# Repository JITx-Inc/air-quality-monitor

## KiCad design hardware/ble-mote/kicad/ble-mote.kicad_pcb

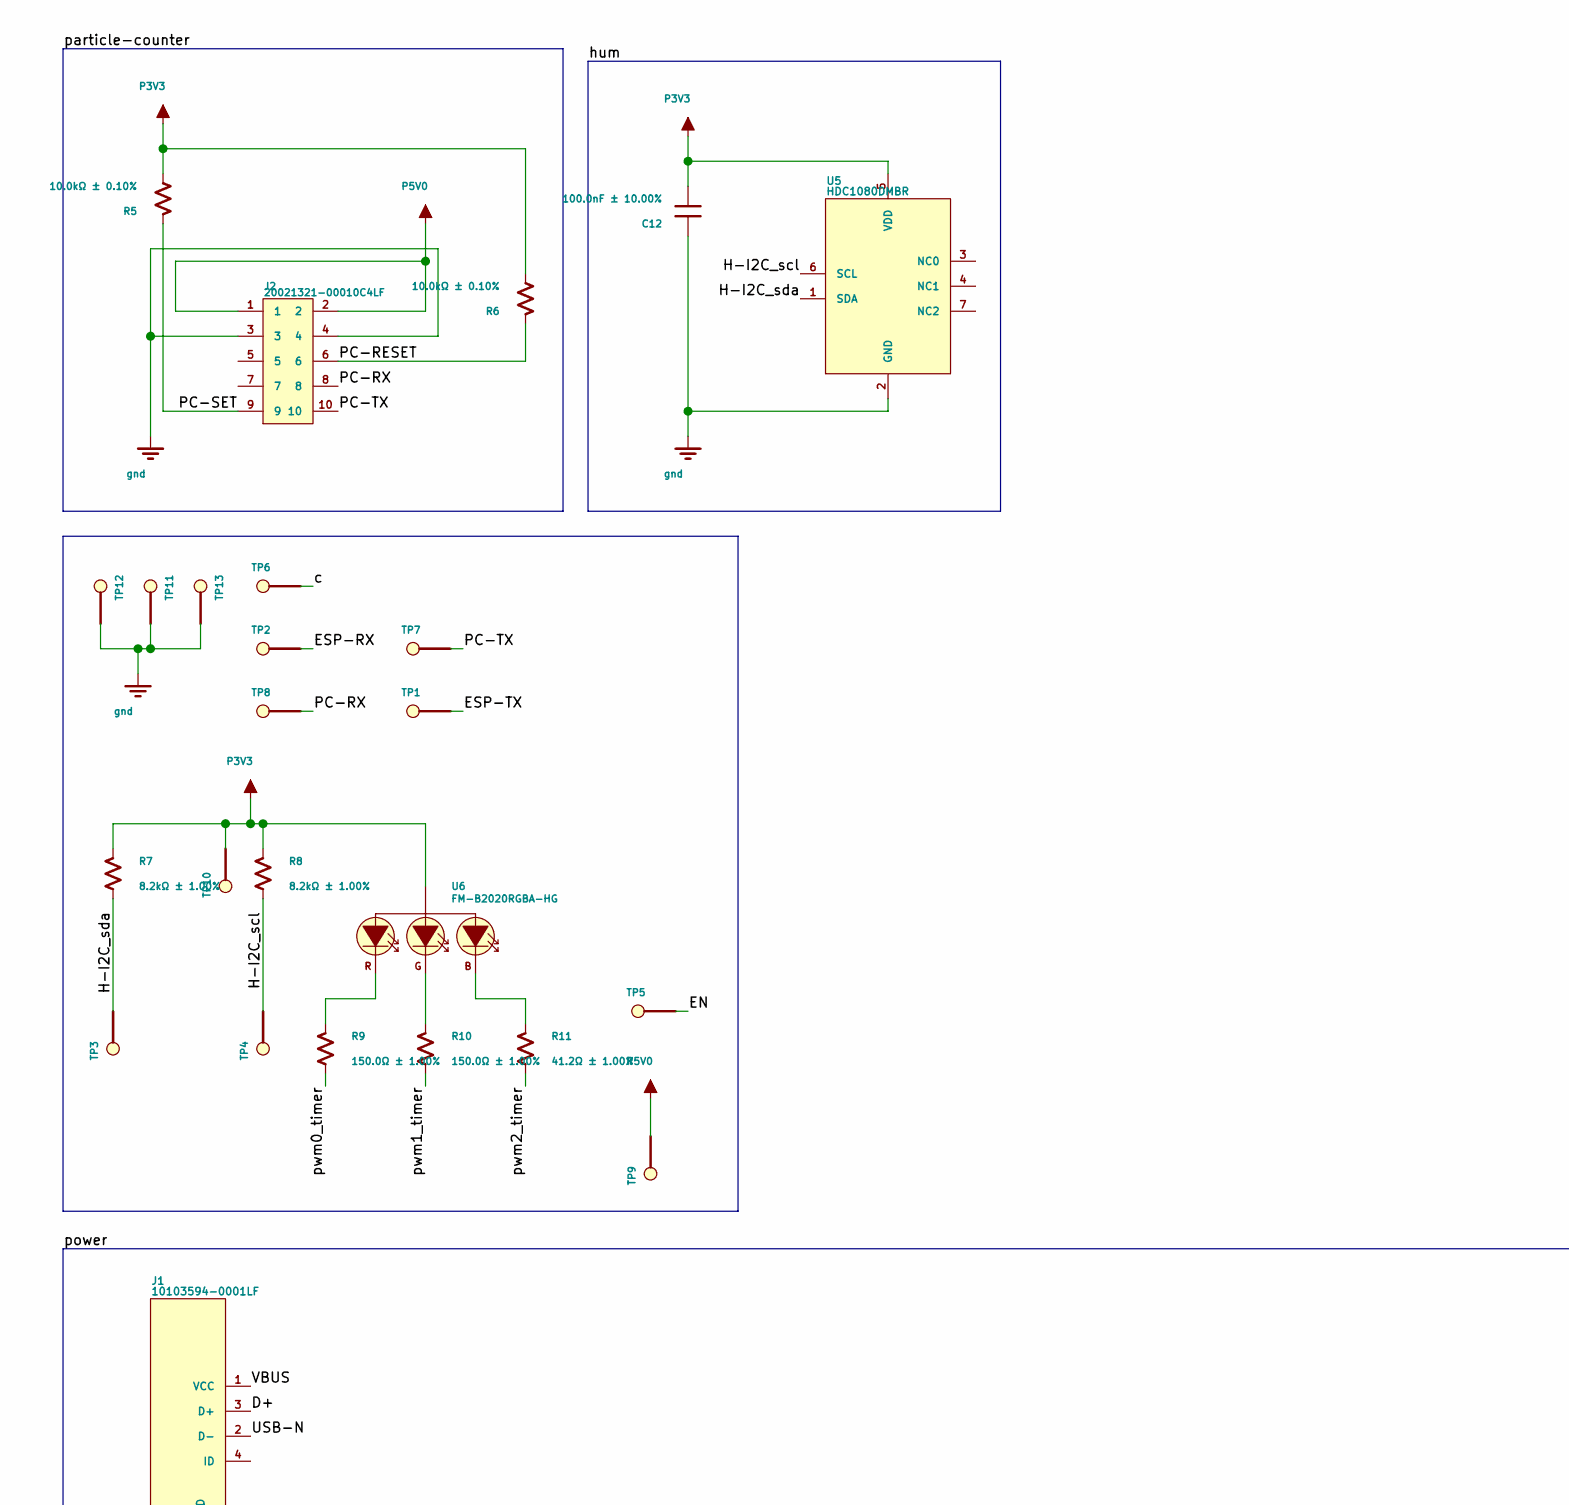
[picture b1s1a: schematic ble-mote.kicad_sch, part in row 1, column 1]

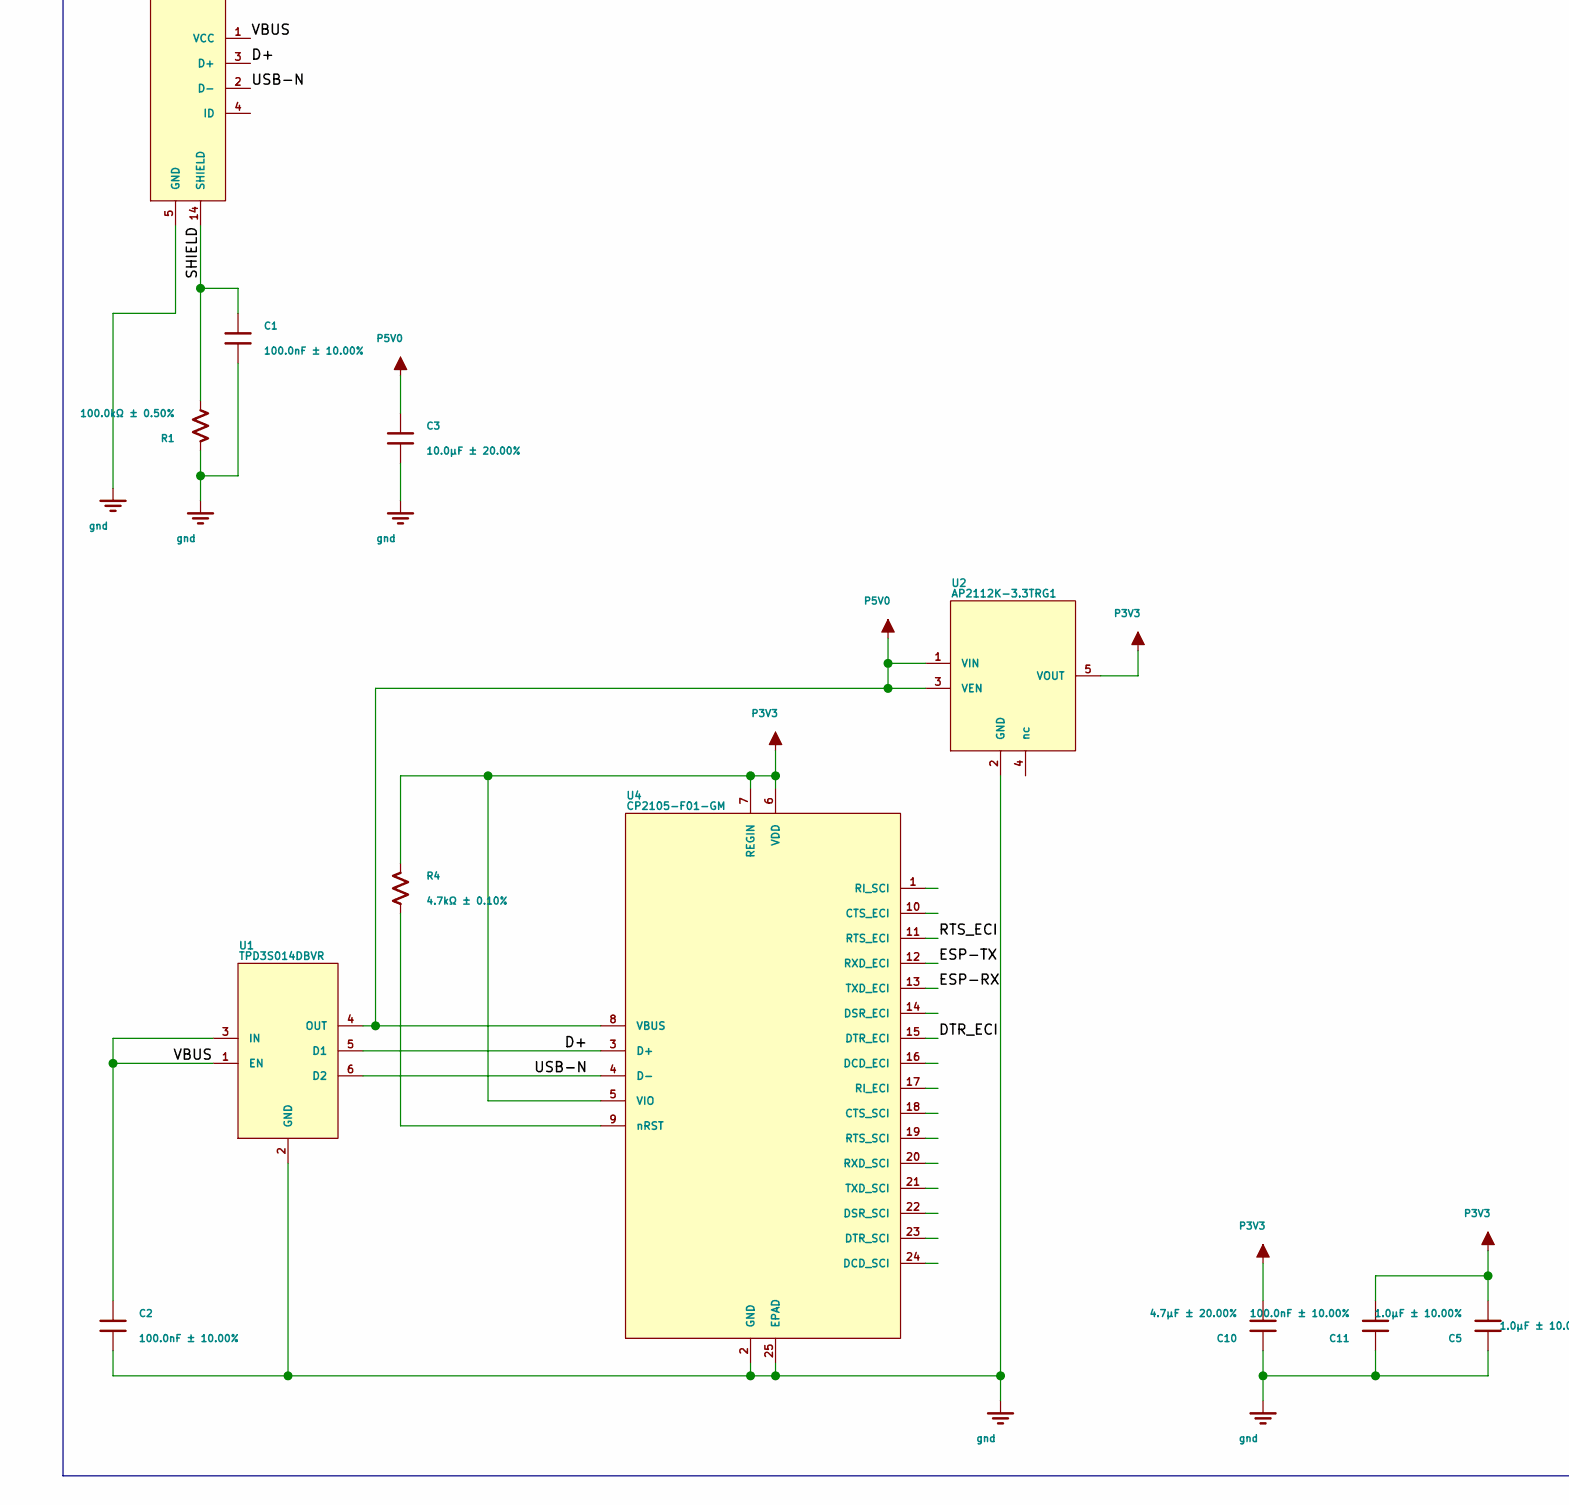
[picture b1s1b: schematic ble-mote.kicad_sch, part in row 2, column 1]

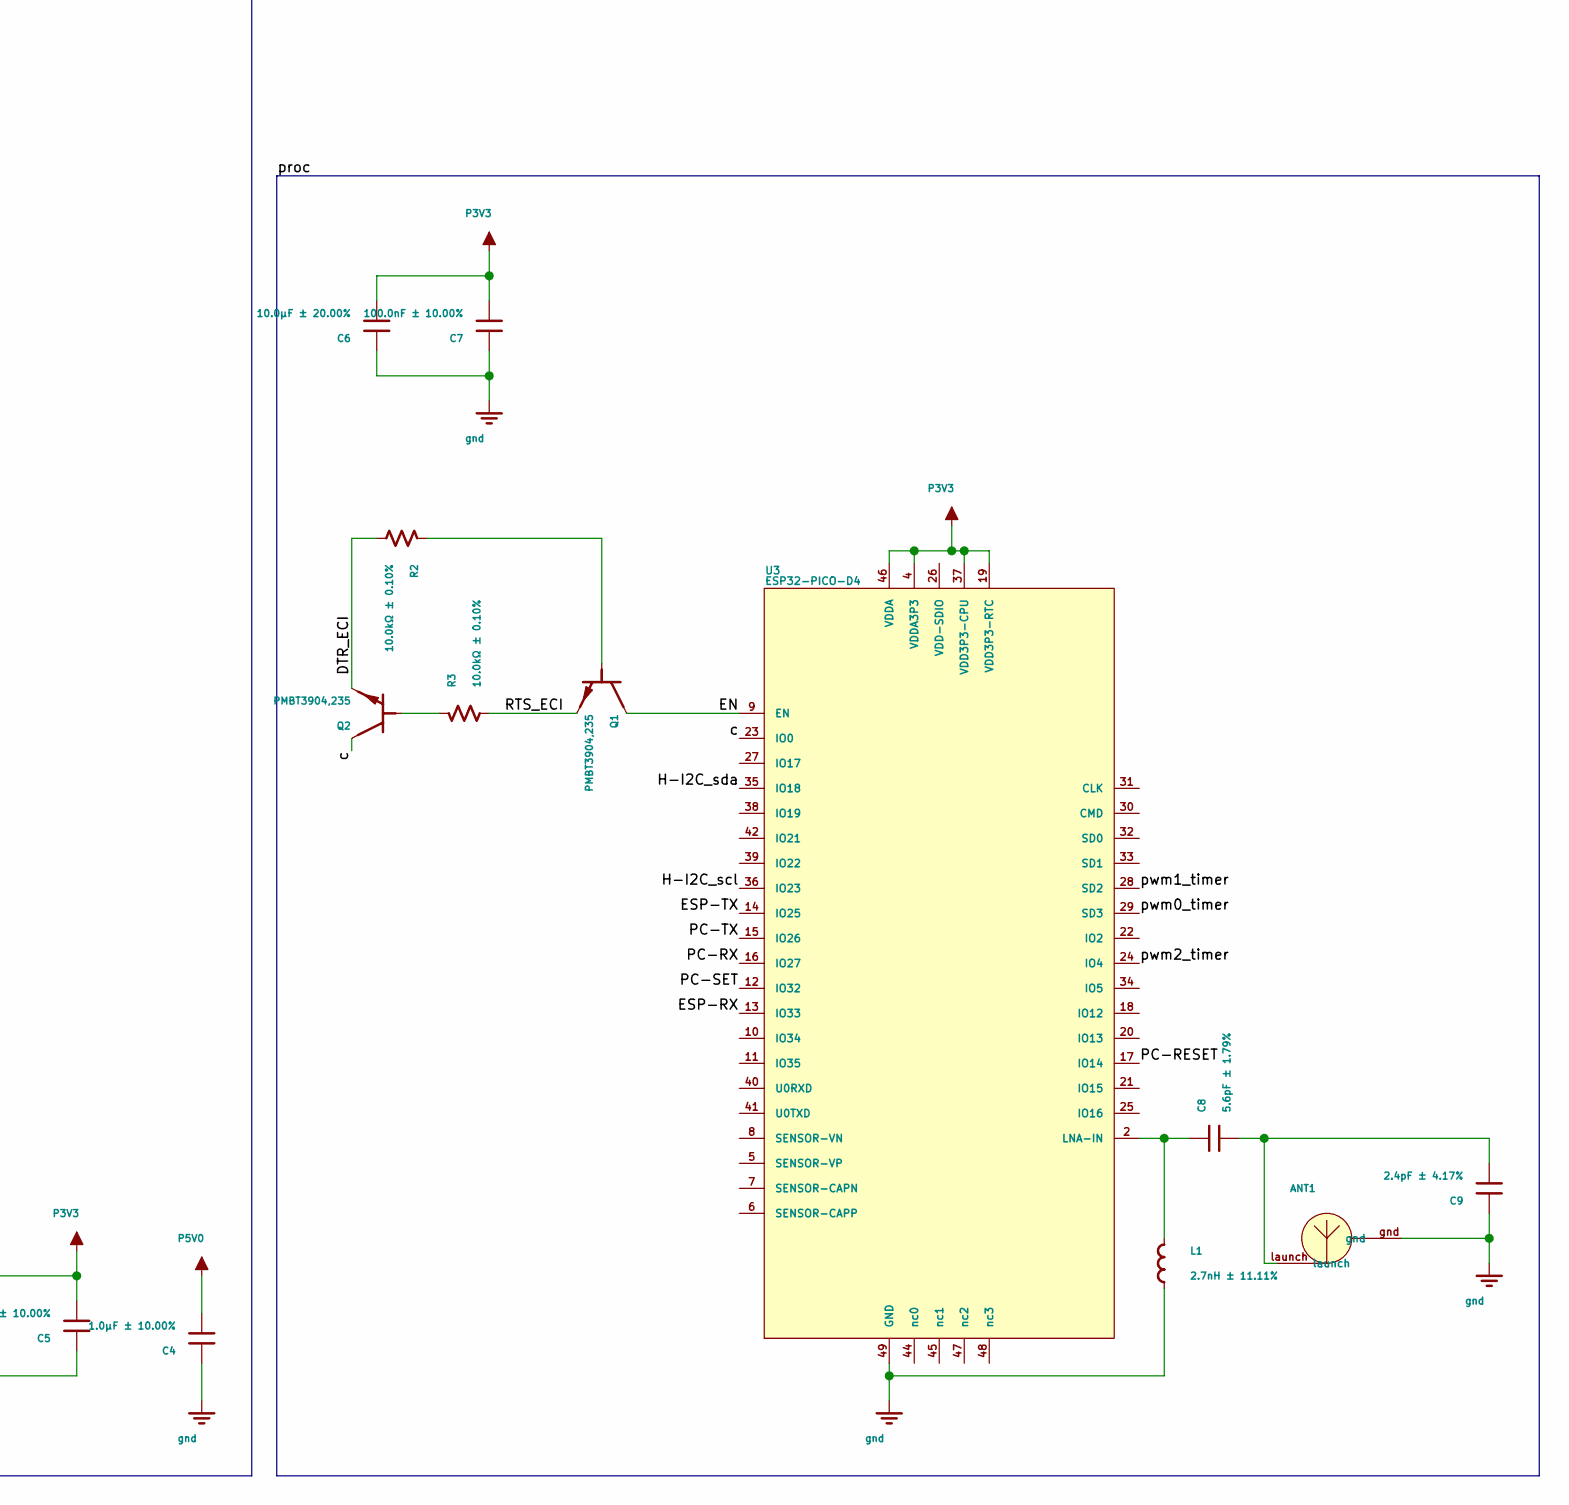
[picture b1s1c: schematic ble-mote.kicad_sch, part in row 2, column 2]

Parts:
ANT1: ant_2GHz4_inverted_f_geom
C1, C2, C7, C11, C12: 100.0nF ± 10.00%; ipc_two_pin_landpattern; Tolerance 10.0%; Maximum Voltage 25.0V; MPN CL05B104KA5NNNC
C3, C6: 10.0μF ± 20.00%; ipc_two_pin_landpattern; Tolerance 20.0%; Maximum Voltage 10.0V; MPN CL05A106MP8NUB8
C4, C5: 1.0μF ± 10.00%; ipc_two_pin_landpattern; Tolerance 10.0%; Maximum Voltage 10.0V; MPN CL05A105KP5NNNC
C8: 5.6pF ± 1.79%; ipc_two_pin_landpattern; Tolerance 1.78571428571429%; Maximum Voltage 50.0V; MPN CL05C5R6BB5NNNC
C9: 2.4pF ± 4.17%; ipc_two_pin_landpattern; Tolerance 4.16666666666667%; Maximum Voltage 50.0V; MPN 04025U2R4BAT2A
C10: 4.7μF ± 20.00%; ipc_two_pin_landpattern; Tolerance 20.0%; Maximum Voltage 10.0V; MPN CL05A475MP5NRNC
J1: 10103594-0001LF; amphenol_10103594_0001lf; MPN 10103594-0001LF
J2: 20021321-00010C4LF; amphenol_minitek127_pkg; MPN 20021321-00010C4LF
L1: 2.7nH ± 11.11%; ipc_two_pin_landpattern; Tolerance 11.1111111111111%; MPN LQG15HS2N7S02D
Q1, Q2: PMBT3904,235; SOT95P280X100_3N; MPN PMBT3904,235
R1: 100.0kΩ ± 0.50%; ipc_two_pin_landpattern; Tolerance 0.5%; MPN RR0510P-104-D
R2, R3, R5, R6: 10.0kΩ ± 0.10%; ipc_two_pin_landpattern; Tolerance 0.1%; MPN MCS0402MD1002BE100
R4: 4.7kΩ ± 0.10%; ipc_two_pin_landpattern; Tolerance 0.1%; MPN RG1005P-472-B-T5
R7, R8: 8.2kΩ ± 1.00%; ipc_two_pin_landpattern; Tolerance 1.0%; MPN CRGCQ0402F8K2
R9, R10: 150.0Ω ± 1.00%; ipc_two_pin_landpattern; Tolerance 1.0%; MPN CRGCQ0402F150R
R11: 41.2Ω ± 1.00%; ipc_two_pin_landpattern; Tolerance 1.0%; MPN ERJ-2RKF41R2X
TP1, TP2, TP3, TP4, TP5, TP6, TP7, TP8, TP9, TP10, TP11, TP12, TP13: RCU-0C; rc_landpattern; MPN RCU-0C
U1: TPD3S014DBVR; SOT95P280X145_6N; MPN TPD3S014DBVR
U2: AP2112K-3.3TRG1; SOT95P280X145_5N; MPN AP2112K-3.3TRG1
U3: ESP32-PICO-D4; pqfn50p700x700x104_49n; MPN ESP32-PICO-D4
U4: CP2105-F01-GM; qfn_landpattern; MPN CP2105-F01-GM
U5: HDC1080DMBR; son100p300x300x80_7n; MPN HDC1080DMBR
U6: FM-B2020RGBA-HG; rgb_2020; MPN FM-B2020RGBA-HG

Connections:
/D+: J1.3 (D+), U1.5 (D1), U4.3 (D+)
/DTR_ECI: Q2.2 (e), R2.1, U4.15 (DTR_ECI)
/EN: Q1.3 (c), TP5.p, U3.9 (EN)
/ESP-RX: TP2.p, U3.13 (IO33), U4.13 (TXD_ECI)
/ESP-TX: TP1.p, U3.14 (IO25), U4.12 (RXD_ECI)
/H-I2C_scl: R8.1, TP4.p, U3.36 (IO23), U5.6 (SCL)
/H-I2C_sda: R7.1, TP3.p, U3.35 (IO18), U5.1 (SDA)
/PC-RESET: J2.6, R6.2, U3.17 (IO14)
/PC-RX: J2.8, TP8.p, U3.16 (IO27)
/PC-SET: J2.9, R5.2, U3.12 (IO32)
/PC-TX: J2.10, TP7.p, U3.15 (IO26)
/RTS_ECI: Q1.2 (e), R3.1, U4.11 (RTS_ECI)
/SHIELD: C1.1, J1.6 (SHIELD), J1.7 (SHIELD), J1.8 (SHIELD), J1.9 (SHIELD), J1.10 (SHIELD), J1.11 (SHIELD), J1.13 (SHIELD), J1.14 (SHIELD), R1.1
/USB-N: J1.2 (D-), U1.6 (D2), U4.4 (D-)
/VBUS: C2.1, J1.1 (VCC), U1.1 (EN), U1.3 (IN)
/c: Q2.3 (c), TP6.p, U3.23 (IO0)
/pwm0_timer: R9.1, U3.29 (SD3)
/pwm1_timer: R10.1, U3.28 (SD2)
/pwm2_timer: R11.1, U3.24 (IO4)
unnamed: ANT1.launch, C8.2, C9.2
unnamed: C8.1, L1.2, U3.2 (LNA-IN)
unnamed: Q1.1 (b), R2.2
unnamed: Q2.1 (b), R3.2
unnamed: R4.1, U4.9 (nRST)
unnamed: R9.2, U6.1 (l_r)
unnamed: R10.2, U6.4 (l_g)
unnamed: R11.2, U6.2 (l_b)
P3V3: C5.2, C6.2, C7.2, C10.2, C11.2, C12.2, R4.2, R5.1, R6.1, R7.2, R8.2, TP10.p, U2.5 (VOUT), U3.1 (VDDA), U3.3 (VDDA3P3), U3.4 (VDDA3P3), U3.19 (VDD3P3-RTC), U3.37 (VDD3P3-CPU), U3.43 (VDDA), U3.46 (VDDA), U4.5 (VIO), U4.6 (VDD), U4.7 (REGIN), U5.5 (VDD), U6.3 (l_a)
P5V0: C3.1, C4.2, J2.1, J2.2, TP9.p, U1.4 (OUT), U2.1 (VIN), U2.3 (VEN), U4.8 (VBUS)
gnd: ANT1.gnd, C1.2, C2.2, C3.2, C4.1, C5.1, C6.1, C7.1, C9.1, C10.1, C11.1, C12.1, J1.5 (GND), J2.3, J2.4, L1.1, R1.2, TP11.p, TP12.p, TP13.p, U1.2 (GND), U2.2 (GND), U3.49 (GND), U4.2 (GND), U4.25 (EPAD), U5.2 (GND)

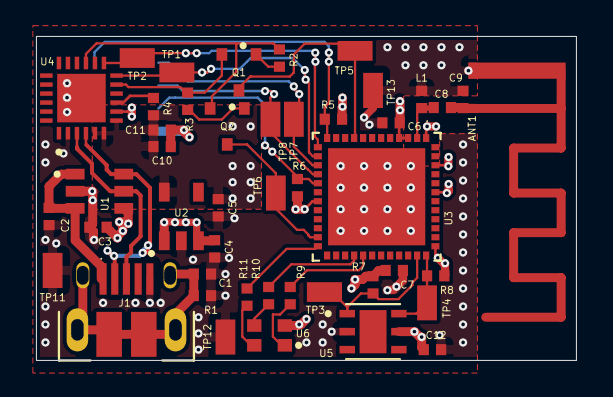
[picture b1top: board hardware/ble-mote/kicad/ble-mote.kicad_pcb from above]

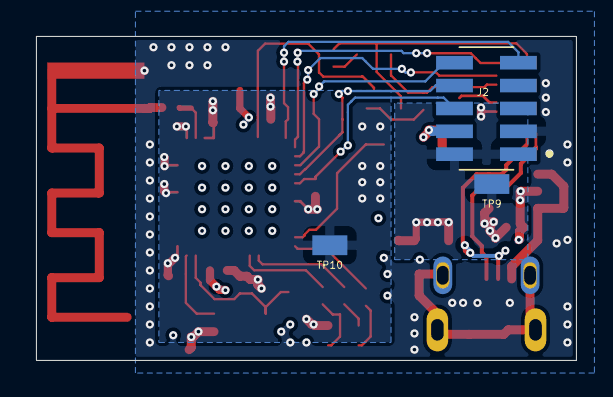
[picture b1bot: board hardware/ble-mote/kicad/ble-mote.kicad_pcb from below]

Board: 4 copper layers, 30.0 x 18.0 mm, 48 parts (3 on the bottom side), 30 nets.

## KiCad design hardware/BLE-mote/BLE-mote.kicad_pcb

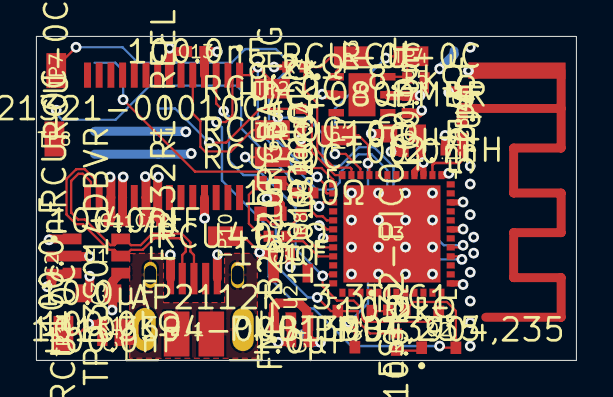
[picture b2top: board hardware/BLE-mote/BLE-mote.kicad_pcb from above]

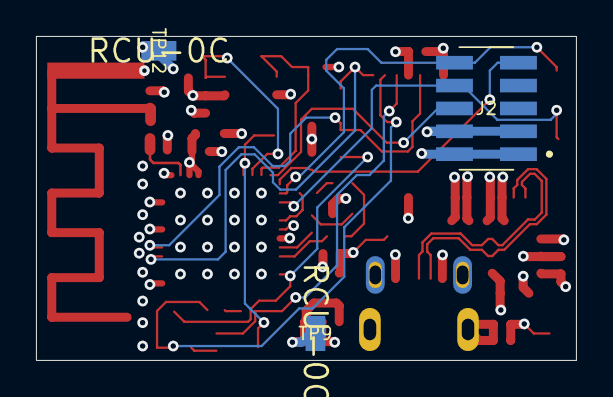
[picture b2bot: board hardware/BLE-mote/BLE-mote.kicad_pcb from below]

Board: 4 copper layers, 30.0 x 18.0 mm, 47 parts (3 on the bottom side), 30 nets.

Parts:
C1, C2, C7, C10, C11, C13: 100.0nF; ipc-two-pin-package$39
C3, C6: 10.0μF; ipc-two-pin-package$51
C4, C5: 1.0μF; ipc-two-pin-package$39
C8: 5.6pF; ipc-two-pin-package$39
C9: 2.4pF; ipc-two-pin-package$39
C12: 4.7μF; ipc-two-pin-package$39
J1: 10103594-0001LF; amphenol-10103594-0001lf
J2: 20021321-00010C4LF; amphenol-minitek127-pkg$89
L1: 2.7nH; ipc-two-pin-package$39
Q1, Q2: PMBT3904,235; SOT95P280X100-3N
R1: 100.0kΩ; ipc-two-pin-package$39
R2, R3, R6, R7: 10.0kΩ; ipc-two-pin-package$39
R4, R5: 8.2kΩ; ipc-two-pin-package$39
R8, R9: 150.0Ω; ipc-two-pin-package$39
R10: 41.2Ω; ipc-two-pin-package$39
TP1, TP2, TP3, TP4, TP5, TP6, TP7, TP8, TP9, TP10, TP11, TP12: RCU-0C; rc-package
U1: TPD3S014DBVR; SOT95P280X145-6N
U2: AP2112K-3.3TRG1; SOT95P280X145-5N
U3: ESP32-PICO-D4; pqfn50p700x700x104-49n
U4: ant-2GHz4-inverted-f-geom
U5: HDC1080DMBR; son100p300x300x80-7n
U6: FM-B2020RGBA-HG; rgb-2020
U7: FT232RL-REEL; sop65-package$121

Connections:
/2: g-sg-0, g-sg-3/PC-RESET: J2.6, R7.2, U3.12
/2: g-sg-0, g-sg-3/PC-RX: J2.8, TP8.p, U3.15
/2: g-sg-0, g-sg-3/PC-SET: J2.9, R6.2, U3.13
/2: g-sg-0, g-sg-3/PC-TX: J2.10, TP7.p, U3.14
/2: g-sg-0, g-sg-3/net_proc_en: Q1.3, TP5.p, U3.9
/2: g-sg-0, g-sg-3/proc_BOOT: Q2.3, TP6.p, U3.23
H-I2C_scl: R5.1, TP4.p, U3.10, U5.6
H-I2C_sda: R4.1, TP3.p, U3.11, U5.1
unnamed: C1.1, J1.6, J1.7, J1.8, J1.9, J1.10, J1.11, J1.13, J1.14, R1.1
unnamed: C8.1, L1.2, U3.2
unnamed: C8.2, C9.2, U4.launch
unnamed: C11.2, U7.17
unnamed: Q1.1, R2.2
unnamed: Q2.1, R3.2
unnamed: R8.1, U3.20
unnamed: R8.2, U6.1
unnamed: R9.1, U3.17
unnamed: R9.2, U6.4
unnamed: R10.1, U3.21
unnamed: R10.2, U6.2
P3V3: C5.2, C6.2, C7.2, C10.2, R4.2, R5.2, R6.1, R7.1, TP10.p, U2.5, U3.1, U3.3, U3.4, U3.19, U3.37, U3.43, U3.46, U5.5, U6.3
P5V0: C3.1, C4.2, C12.2, C13.2, J2.1, J2.2, TP9.p, U1.4, U2.1, U2.3, U7.4, U7.20
gnd: C1.2, C2.2, C3.2, C4.1, C5.1, C6.1, C7.1, C9.1, C10.1, C11.1, C12.1, C13.1, J1.5, J2.3, J2.4, L1.1, R1.2, TP11.p, TP12.p, U1.2, U2.2, U3.49, U4.gnd, U5.2, U7.7, U7.18, U7.21, U7.25
net_proc_uart_dtr: Q2.2, R2.1, U7.2
net_proc_uart_rts: Q1.2, R3.1, U7.3
proc_ESP-RX: TP2.p, U3.40, U7.1
proc_ESP-TX: TP1.p, U3.41, U7.5
usb_D+: J1.3, U1.6, U7.15
usb_D-: J1.2, U1.5, U7.16
usb_VBUS: C2.1, J1.1, U1.1, U1.3

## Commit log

2020-12-22 Copy ble-mote from ocdb
2020-12-22 Use grouped placement
2020-12-22 Inital commit of CAD
2020-12-22 Rearranging schematic
2020-12-22 Schematic cleaned up
2020-12-22 Place and routing
2020-12-22 Adding signal transitions
2020-12-23 Top layer routed
2020-12-23 Bottom layer routed, mostly without compromise
2020-12-23 DRC clean without pin reassignment on mcu
2020-12-24 Pins reassigned
2020-12-24 DRC clean with pins reassigned
2021-10-13 Check in initial hardware for layout
2021-10-13 Remove dat file
2021-10-28 Ignore kicad backups and autosaves
2021-10-28 WIP, before updating from schematic for pin swaps
2021-10-29 WIP, still before updating from schematic
2021-10-29 Update PCB from schematic, to get desired pin mapping on ESP32
2021-10-29 Fixed error in pin mapping and connected the new pins
2021-10-29 finished draft, more or less — ready for review
2021-11-02 third revision
2021-11-02 Moved values to fab, fixed spacing around humidity sensor, fixed up silkscreen
2021-11-03 Fixed some silkscreen issues
